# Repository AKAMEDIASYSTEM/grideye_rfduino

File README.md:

grideye_rfduino
===============

a tiny 8x8 thermal camera with OLED display and BLE capability

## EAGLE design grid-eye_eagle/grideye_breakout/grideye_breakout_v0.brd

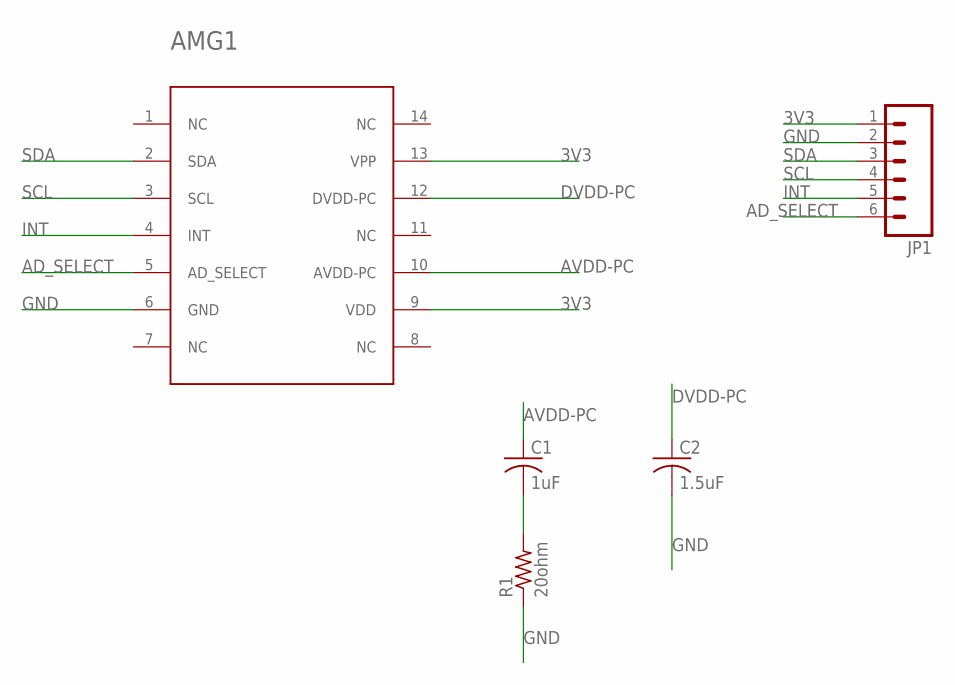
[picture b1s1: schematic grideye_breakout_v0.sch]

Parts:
AMG1: AMG8831
C1: 1uF; C0805
C2: 1.5uF; C0805
JP1: M06LOCK_LONGPADS; 1X06_LOCK_LONGPADS
R1: 20ohm; M0805

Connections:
3V3: AMG1.9 (VDD), AMG1.13 (VPP), JP1.1
AD_SELECT: AMG1.5 (AD_SELECT), JP1.6
AVDD-PC: AMG1.10 (AVDD-PC), C1.1
DVDD-PC: AMG1.12 (DVDD-PC), C2.1
GND: AMG1.6 (GND), C2.2, JP1.2, R1.1
INT: AMG1.4 (INT), JP1.5
unnamed: C1.2, R1.2
SCL: AMG1.3 (SCL), JP1.4
SDA: AMG1.2 (SDA), JP1.3

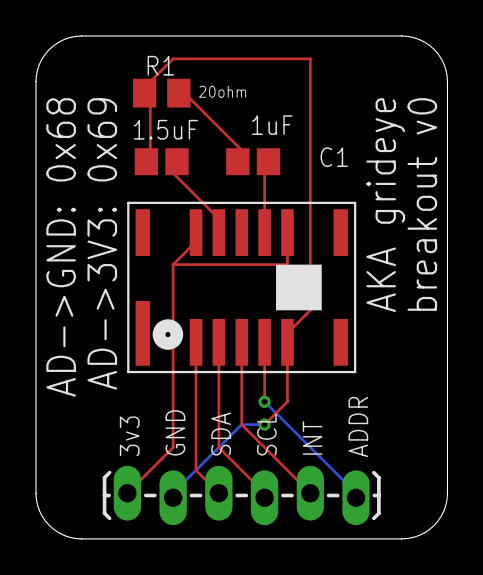
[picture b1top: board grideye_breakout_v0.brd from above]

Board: 2 copper layers, 22.9 x 27.9 mm, 5 parts (0 on the bottom side), 9 nets.

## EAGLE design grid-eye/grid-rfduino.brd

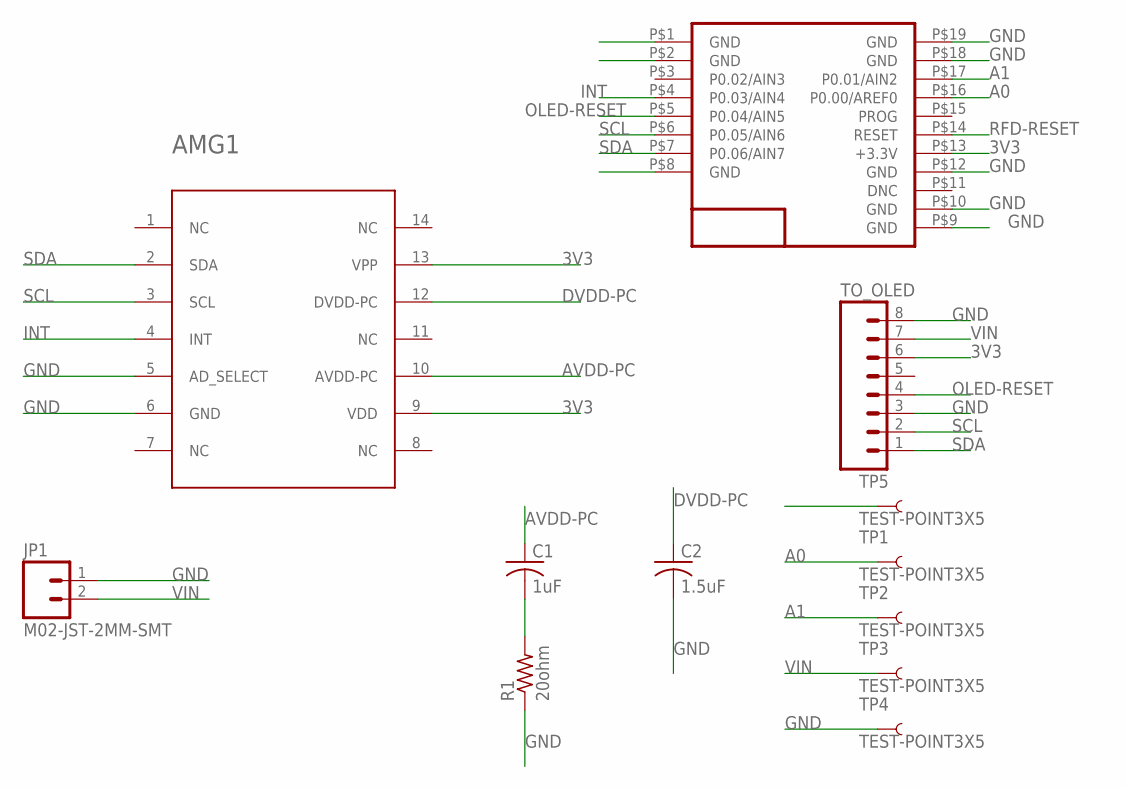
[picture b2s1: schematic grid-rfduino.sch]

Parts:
AMG1: AMG8831
C1: 1uF; C0805
C2: 1.5uF; C0805
JP1: M02-JST-2MM-SMT; JST-2-SMD
R1: 20ohm; M0805
TO_OLED: M08LOCK; 1X08_LOCK
TP1, TP2, TP3, TP4, TP5: TEST-POINT3X5; PAD.03X.05
U$1: RFD22301; RFD21733

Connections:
3V3: AMG1.9 (VDD), AMG1.13 (VPP), TO_OLED.6, U$1.P$13 (+3.3V)
A0: TP1.P$1, U$1.P$16 (P0.00/AREF0)
A1: TP2.P$1, U$1.P$17 (P0.01/AIN2)
AVDD-PC: AMG1.10 (AVDD-PC), C1.1
DVDD-PC: AMG1.12 (DVDD-PC), C2.1
GND: AMG1.5 (AD_SELECT), AMG1.6 (GND), C2.2, JP1.1 (2), R1.1, TO_OLED.3, TO_OLED.8, TP4.P$1, U$1.P$1 (GND), U$1.P$2 (GND), U$1.P$8 (GND), U$1.P$9 (GND), U$1.P$10 (GND), U$1.P$12 (GND), U$1.P$18 (GND), U$1.P$19 (GND)
INT: AMG1.4 (INT), U$1.P$4 (P0.03/AIN4)
unnamed: C1.2, R1.2
OLED-RESET: TO_OLED.4, U$1.P$5 (P0.04/AIN5)
RFD-RESET: TP5.P$1, U$1.P$14 (RESET)
SCL: AMG1.3 (SCL), TO_OLED.2, U$1.P$6 (P0.05/AIN6)
SDA: AMG1.2 (SDA), TO_OLED.1, U$1.P$7 (P0.06/AIN7)
VIN: JP1.2 (1), TO_OLED.7, TP3.P$1

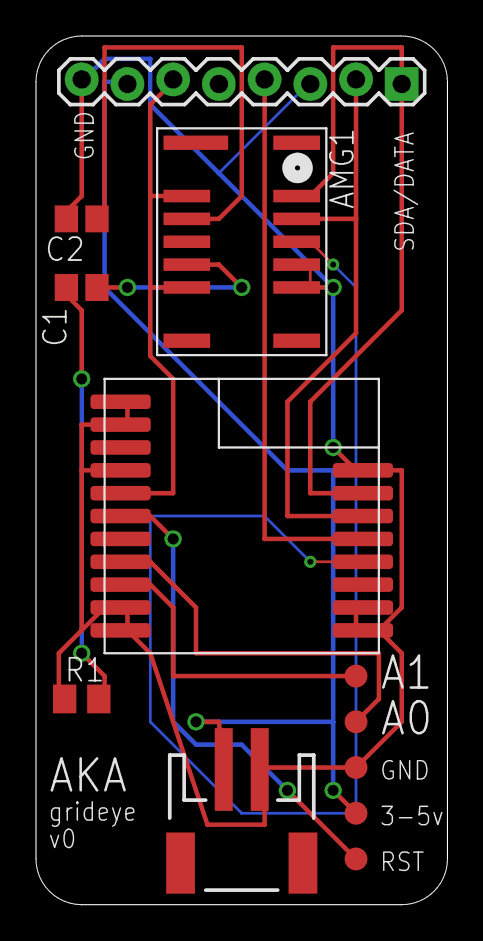
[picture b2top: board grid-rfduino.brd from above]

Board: 2 copper layers, 22.9 x 48.3 mm, 12 parts (0 on the bottom side), 13 nets.

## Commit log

2014-04-19 first commit, added eagle files
2014-04-20 reorganizing files
2014-04-20 added rfduino firmware
2014-04-20 adding media for README
2014-04-20 added media, maybe
2014-04-20 more media
2014-04-20 added bom
2014-05-28 updated UI to include full resolution. mitigated but did not eradicate ranging bug
2014-05-28 oops removed license; added it back in
2014-08-06 adding breakout board

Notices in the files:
parts and their libraries:
SparkFun-Connectors: Licensing: CC v3.0 Share-Alike You are welcome to use this library for commercial purposes.
